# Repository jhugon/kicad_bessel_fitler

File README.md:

# LC Bessel Filter in KiCAD

3th order Pi filter with 50 ohm in/out impedance

E24 series caps seems available as 1% 1206.

Coilcraft makes variable inductors and fixed 1206CS series in E12 values.

From SPICE studies on 10 MHz, it seems that even 5% values for all components
will be fine. There is already a bit of ripple at the end of the impulse
response, and the component variation is smaller than the ripple.

I'm going to make a main branch with a variable inductor as well as another
branch with a 1206CS fixed inductor.

## For 6 MHz

27 ns time const and 58 ns rise time

- L1 = 1u287
- C1 = 179p
- C2 = 1n169

Parts:

- L1 = 143-18J12L (unshielded over 1 uH)
- C1 = 180p
- C2 = 1200p

## 10 MHz

16 ns time const and 35 ns rise time.

- L1 = 772n3
- C1 = 107p4
- C2 = 701p4

Parts:

- L1 = 143-17J12SL
- C1 = 110p
- C2 = 680p

## 20 MHz

8 ns time const and 16 ns rise time

- L1 = 386n2
- C1 = 53p70
- C2 = 350p7

Parts:

- L1 = 143-09J12SL
- C1 = 56p
- C2 = 360p

## 40 MHz

4 ns time const and 8.8 ns rise time

- L1 = 193n1
- C1 = 26p85
- C2 = 175p3

Parts:

- L1 = 144-07J12SL
- C1 = 27p
- C2 = 180p

# Sychronously Tuned Filter

For each section:

Q = Qtot * sqrt(2^(1/n)-1)

or

BW = BWtot * sqrt(2^(1/n)-1)

For n = 3, 5, and 7, the sqrt term is: 0.6436, 0.3856, 0.3226

zeta = 2Q, so critically damped is Q = 0.5

So critically damped section Q for n = 3, 5, 7 is: 0.3218, 0.1928, 0.1613

For 10 MHz BWtot, BW for each section for n = 3, 5, 7 is: 6.436, 3.856, 3.226 MHz

A critically damped RLC LP filter has C = 1/(2R omega_0) and L = 2R/(omega_0).
So for 10 MHz and R = 50 ohms: C = 159.2p and L = 1.592u. That would seem to
give an input and output impedance of 100 ohms from Z = sqrt(L/C). Cutting the
total C in half across a pi network may help? But then this Pi network will
have the wrong BW and Q?

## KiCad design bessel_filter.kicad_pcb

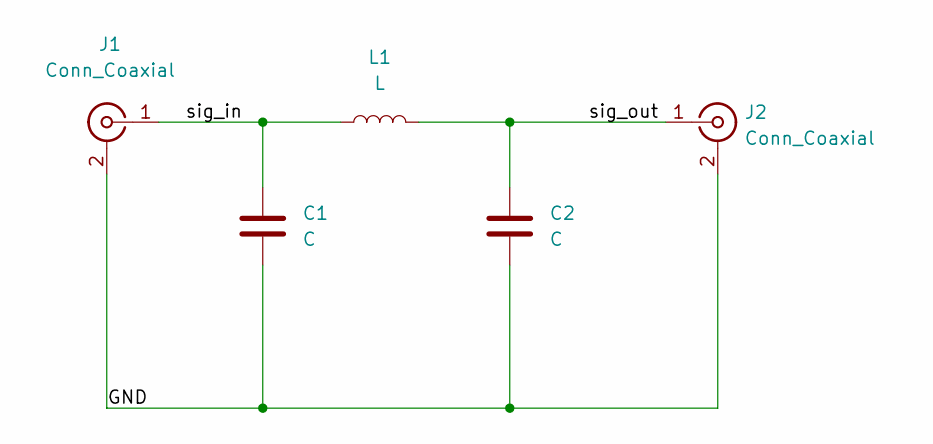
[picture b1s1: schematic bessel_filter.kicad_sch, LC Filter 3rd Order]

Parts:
C1, C2: C; C_1206_3216Metric_Pad1.33x1.80mm_HandSolder
J1, J2: Conn_Coaxial; SMA_Amphenol_132289_EdgeMount
L1: L; L_1206_3216Metric_Pad1.42x1.75mm_HandSolder

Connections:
/GND: C1.2, C2.2, J1.2 (Ext), J2.2 (Ext)
/sig_in: C1.1, J1.1 (In), L1.1
/sig_out: C2.1, J2.1 (In), L1.2

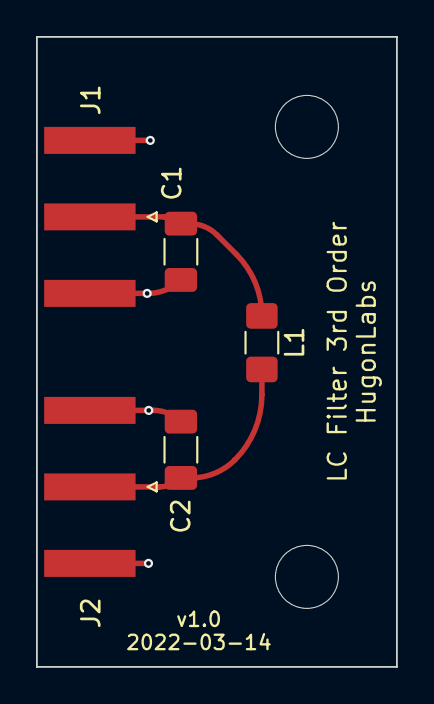
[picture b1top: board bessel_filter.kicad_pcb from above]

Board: 2 copper layers, 20.0 x 35.0 mm, 5 parts (0 on the bottom side), 3 nets.

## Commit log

2022-03-10 added scaled L/C values
2022-03-12 Added README
    with info
    fixed L1 value in schematic
2022-03-12 Added some other freqs/component values to README
2022-03-12 switched to 3rd order filter for simplicity
    component values are moved from schematic to README.md
2022-03-12 Added filter_response.py and spice submodule
    and spice_template.cir
2022-03-13 filter_response.py: variational analysis on component vals
2022-03-13 progress on PCB--need to add L shield to ground connections
2022-03-13 PCB finished
2022-03-13 Added gerbers
2022-03-14 Finished layout for 3rd order-fixed L
2022-03-14 Updated gerbers for 3O-Lfixed
2022-03-15 working on synch tuned filter
2022-04-22 updates in spice/
